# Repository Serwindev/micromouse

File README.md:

# Project Zacch v1

## About the project

Project Zacch is a full-size micromouse whose aim is to solve the maze autonomously.

The name of the mouse actually comes from Bible (Luke 19:1-10). There was a man called Zacchaeus -- who wanted to see Jesus but because he was short, he couldn't able to see Him. So he climbed a tree to see Jesus.

The dimension of Zacch is 90mm x 127mm (3.54 x 5.00 inches). Compared to other mice out there, it isn't that small. But this is my first-ever hardware project and i needed some more space to work properly.

The Project Zacch v1 is a project made for the event ["Fallout"](https://fallout.hackclub.com/) conducted by [HackClub](https://hackclub.com/).

---

## BOM

|sno|product name         |description                                  |Quantity |link                                                                                                                                                                                                                                                                                                                                                                                             |unit price |amount |Running total |   |
|---|---------------------|---------------------------------------------|---------|-------------------------------------------------------------------------------------------------------------------------------------------------------------------------------------------------------------------------------------------------------------------------------------------------------------------------------------------------------------------------------------------------|-----------|-------|--------------|---|
|  1| ESP32               | Brain of the Mouse                          |        1| [link](https://makerbazar.in/products/esp32-wroom-wifi-ble-bluetooth-iot-node-mcu-board?variant=48251049935088)                                                                                                                                                                                                                                                                                         |     445.00| 445.00|        445   |   |
|  2| Motor Driver        | Bridge between Brain and motor              |        1| [link](https://makerbazar.in/products/drv8833-2-channel-1-5a-dc-motor-driver?variant=48341841346800)                                                                                                                                                                                                                                                                                                    |      65.00|  65.00|        510   |   |
|  3| Motors with encoders| Locomotive device to calculate it's position|        2| [link](https://roboticsdna.in/product/n20-6v-500rpm-micro-metal-gear-motor-with-encoder/ )                                                                                                                                                                                                                                                                                                              |     494   | 988   |       1498   |   |
|  4| Infrared Sensors    | Eyes to watch out for obstacles             |        2| [link](https://makerbazar.in/products/ir-receiver-transistor-led?variant=42847315525872)                                                                                                                                                                                                                                                                                                                |      99.00| 198   |       1696   |   |
|  5| Battery             | To power the mouse                          |        1| [link](https://robu.in/product/wly603040-600mah-3-7v-single-cell-rechargeable-lipo-battery/?utm_source=chatgpt.com)                                                                                                                                                                                                                                                                                     |     198   | 198   |       1894   |   |
|  6| MOSFET              | To switch on the IR leds                    |        2| [link](https://www.digikey.in/en/products/detail/alpha-omega-semiconductor-inc/AO3400A/1855772)                                                                                                                                                                                                                                                                                                         |      49.15|  98.30|       1992.3 |   |
|  7| Resistors pack      | TO limit the current                        |        1| [link](https://robu.in/product/30-different-valued-metal-film-resistor-assorted-kit-for-diy-electronic-projects-and-experiments/)                                                                                                                                                                                                                                                                       |     199.00| 199.00|       2191.3 |   |
|  8| Wheels              | Pair of wheels suitable for N20             |        1| [link](https://dyoraarobotics.in/product/2)                                                                                                                                                                                                                                                                                                                                                             |     269   | 269   |       2460.3 |   |
|  9| Caster ball         | Non-driven wheel to support the mouse       |        1| [link](https://makerbazar.in/products/mini-3pi-car-n20-caster-robot-ball-wheel)                                                                                                                                                                                                                                                                                                                         |      39   |  39   |       2499.3 |   |
| 10| Boost converter     | To convert low voltage into 5v              |        1| [link](https://robocraze.com/products/tps61023-3-7a-5v-output-mini-boost-converter-breakout-board-7semi?srsltid=AfmBOorZcjLyfdjhu4-ktQiGOcvzMeDhyjm8kQI_HV5Uemv6zVHmJe5q)                                                                                                                                                                                                                               |      87   |  87   |       2586.3 |   |
| 11| Switch              | To power ON/OFF                             |        1| [link](https://makerbazar.in/products/3-pin-dip-mini-slide-switch-through-hole-pcb-slide-button?variant=46800238575856)                                                                                                                                                                                                                                                                                 |      55   |  55   |       2641.3 |   |
| 12| Screw terminal      | To connect battery                          |        1| [link](https://makerbazar.in/products/wire-to-board-screw-terminal-connectors?srsltid=AfmBOorlYyyEAAogTVcPhF7FhGmk6QyMP0Ij64HXCppaQqRuH7ws5u8H&variant=48816549658864)                                                                                                                                                                                                                                  |      25   |  25   |       2666.3 |   |
| 13| Capacitor 47uF      | Caps to store energy                        |        3| [link](https://www.mouser.in/en/ProductDetail/Panasonic/ECA-1HHG470?qs=sGAEpiMZZMsh%252B1woXyUXj0KTxVgEP8%2FoesVWFq9mWps%3D)                                                                                                                                                                                                                                                                            |      17.89|  53.67|       2719.97|   |
| 14| Capacitor 0.1uF     | Caps                                        |       10| [link](https://robu.in/product/rder71h104k0m1h03a-murata-electronics-%C2%B110-50v-100nf-x7r-pluginp5mm-multilayer-ceramic-capacitors-mlcc-leaded-rohs/?gad_source=1&gad_campaignid=17427802703&gbraid=0AAAAADvLFWefn6i5u6u06P2ikuNaq8nHi&gclid=CjwKCAjwvNfSBhBiEiwAyaGMCc8RoM_25v4rTFsFHUdJuWaXGIPravkARzQQLWtrZbm0opEAT2KkExoCW2IQAvD_BwE)                                                             |      16.00| 160   |       2879.97|   |
| 15| Female headers      | To mount componenets                        |        3| [link](https://makerbazar.in/products/female-berg-strip-2-54mm-header-pin?variant=46822716735728&country=IN&currency=INR&utm_medium=product_sync&utm_source=google&utm_content=sag_organic&utm_campaign=sag_organic&gad_source=1&gad_campaignid=17426677322&gbraid=0AAAAACLxaAblJEnB5dLql7-x3ZBpJzfe3&gclid=CjwKCAjwmdLSBhANEiwAkREMN3OXcRsLFpE1FGKxTkcoRNSS2PXJgUW0fRO1fCnhbYDCYuGI9XgbIRoCBOQQAvD_BwE)|       8.5 |  25.50|       2905.47|   |
| 16| Male headers        | To mount components                         |        2| [link](https://makerbazar.in/products/berg-strip-40-pins?variant=49811925532912&country=IN&currency=INR&utm_medium=product_sync&utm_source=google&utm_content=sag_organic&utm_campaign=sag_organic&gad_source=1&gad_campaignid=17426677322&gbraid=0AAAAACLxaAblJEnB5dLql7-x3ZBpJzfe3&gclid=CjwKCAjwmdLSBhANEiwAkREMNz77SH8W3c11Vlf4g-hZFOluHlT7KyqQvG2HieT2qgm2LeFkTQocnRoCc5MQAvD_BwE)                 |      25   |  50   |       2955.47|   |
| 17| Tactile switch      | To actually make mouse move                 |        1| [link](https://makerbazar.in/products/small-push-button-switch?srsltid=AfmBOoqmTbENfx2a-pJnI3aoowbEo9liCWUeOjVfWND0_L68pnGFyOcG)                                                                                                                                                                                                                                                                        |      20   |  20   |       2975.47|   |
| 18  | PCB                  | Acts as a chassis as well as electrical circuit | 1        | wherever you prefer                                                                                                                                                                                                                                                                                                                                                                              | 3500       | 3500   | 6475.47       |   |
| 19  | 3d print             | Mounts for motors                               | 2        | wherever you prefer (use assets/CAD_design/Motot_mount.stp)                                                                                                                                                                                                                                                                                                                                      | 500        | 1000   | 7475.47       |   |

---

## Project Workflow

I have actually journalled everything from Day 1 till the end -- you can find them in the **Devlogs folder**.

#### Research and Development

- On the Day 1, i worked on researching the requirments for the project.
- On further days, i sourced online to find the suitable products and built the BOM (Bill of materials) -- which you can find [here](components/BOM.csv) and also sketched a very rough diagram about the wiring.

---

#### Schematic 

- From day 4, i worked on the Schematic design in Kicad. It's my very first time and i found it kinda hard at first.
- After some several iterations and struggles, with the help of chatGPT, i finished the 1st version of schematic on day 7

---

#### CAD design

- From Day 8, i worked on the CAD design of this project in Tinkercad
- After two days of CAD'ing, i somehow managed to capture the vision in my mind into the Screen. (Spoiler alert: Final result isn't the same as here)

---

#### PCB design

- After the completion of CAD design, i started to add footprints for all the componenets in kicad.
- I found it hard to understand the way footprint works in the consecutive days.
- During these days, i changed the IR sensors - from modules to separate transmiter. (Reason: Because the module provides only True or False output based on whether the obstacle is near or not)
- I completed the whole routing of PCB by the day 20, but then i found that esp32 has been misaligned and needs to be re-aligned.
- After two days of debugging, i completed the PCB (But still, I thought of adding some LED's into the PCB and mounting Pads for caster ball)

##### Front copper

##### Back copper

##### Final routing 

PS: There's an easter egg in the PCB -- if you can find it out and DM me for prizes!! 
Instagram: [@serwin.dev](https://www.instagram.com/serwin.dev)

---

### Features

- Project Zacch uses two driven wheels and a non-driven caster ball for locomotion.
- It uses IR sensors and transmitter to wall sensing mechanism.

---

## How to build?!

- Step 1: Check whether you have all the components
- Step 2: Order PCB and wait -- take some rest
- Step 3: Quickly assemble all the parts
- Step 4: Run firmware and GOOO!!!!

---

### Future works

- Once the build is successful, the firmware of the project will commence.
- Using PID for staying in the center of the line.

---

### Contributors

- [@Serwindev](https://github.com/Serwindev)

---

### Resources

- [Ojasp21/micromouse](https://github.com/Ojasp21/Micromouse/tree/main)
- [Mushak/micromouse](https://github.com/gautam-dev-maker/mushak/tree/main)

---

### Special Credits

- All thanks to HackClub for making this project came into life through [Fallout](https://fallout.hackclub.com/)

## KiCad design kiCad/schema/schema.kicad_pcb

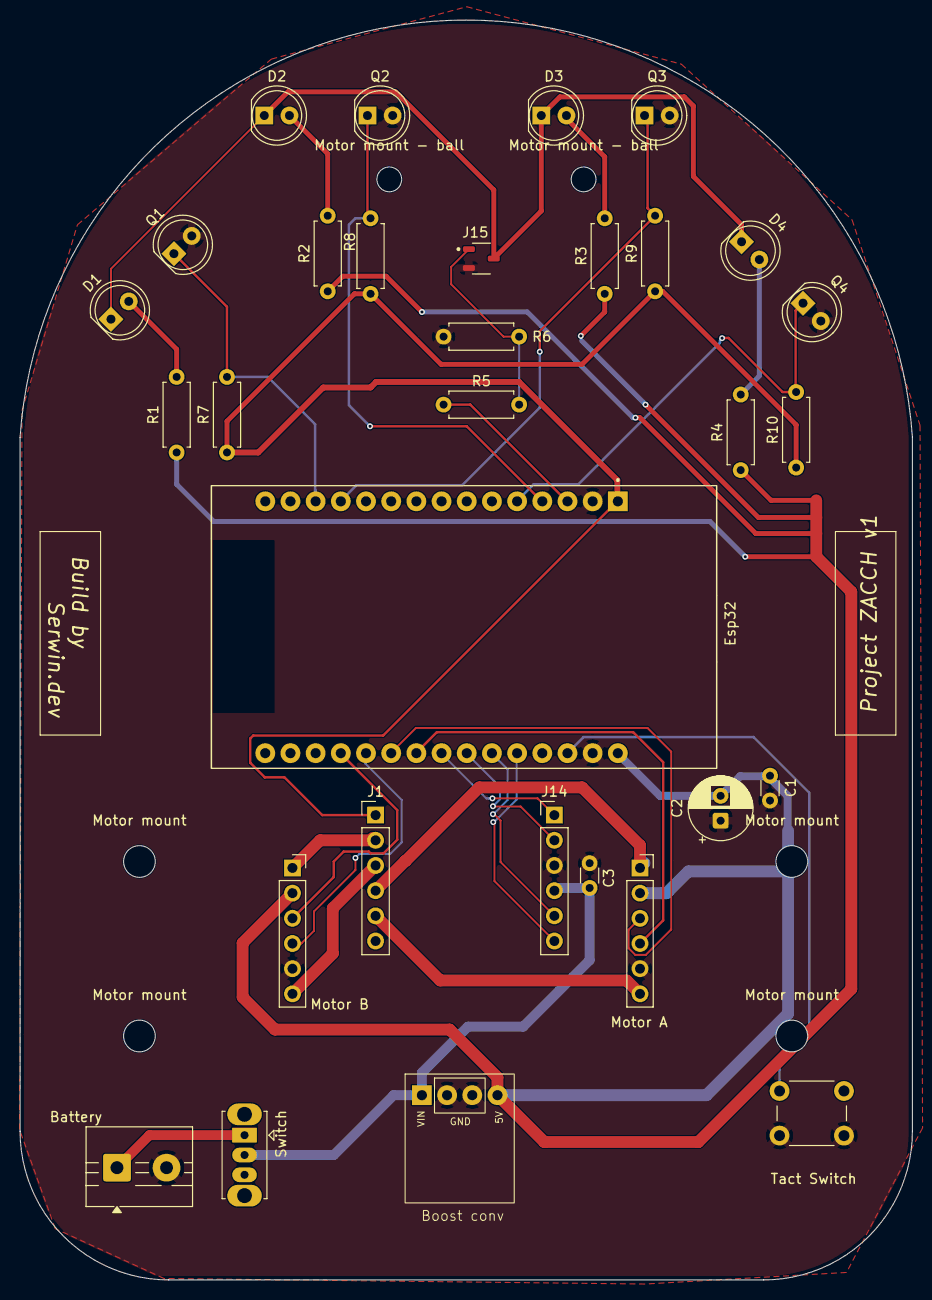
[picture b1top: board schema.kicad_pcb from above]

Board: 2 copper layers, 90.0 x 127.1 mm, 37 parts (0 on the bottom side), 29 nets.

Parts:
Battery: Bat; TerminalBlock_MaiXu_MX126-5.0-02P_1x02_P5.00mm
Boost conv: BOOST; TPS61023
C1, C3: C 0.1; C_Disc_D3.0mm_W1.6mm_P2.50mm
C2: C_Polarized 47; CP_Radial_D6.3mm_P2.50mm
D1, D2, D3, D4: LED; LED_D5.0mm_Clear
Esp32: Esp32; MODULE_ESP32_DEVKIT_V1
J1: DRV8833; PinHeader_1x06_P2.54mm_Vertical
J14: GND; PinHeader_1x06_P2.54mm_Vertical
J15: MOSFET; SOT95P280X125-3N
Motor A: M2 Left; PinSocket_1x06_P2.54mm_Vertical
Motor B: M1 Right; PinSocket_1x06_P2.54mm_Vertical
Motor mount: MountingHole_3.2mm_M3
Motor mount - ball: MountingHole_2.5mm
Motor mount - ball#2: MountingHole_2.5mm
Motor mount#2, Motor mount#3, Motor mount#4: MountingHole_3.2mm_M3
Q1, Q2, Q3, Q4: Q_Photo_NPN; LED_D5.0mm_Clear
R1, R2, R3, R4: 120 ohm; R_Axial_DIN0207_L6.3mm_D2.5mm_P7.62mm_Horizontal
R5: 100 ohm; R_Axial_DIN0207_L6.3mm_D2.5mm_P7.62mm_Horizontal
R6: 100k ohm; R_Axial_DIN0207_L6.3mm_D2.5mm_P7.62mm_Horizontal
R7, R8, R9, R10: 10k ohm; R_Axial_DIN0207_L6.3mm_D2.5mm_P7.62mm_Horizontal
Switch: Switch; SW_Slide_SPDT_Straight_CK_OS102011MS2Q
Tact Switch: Tact Switch; SW_PUSH_6mm_H5mm

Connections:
/3V3: Esp32.1, J1.1, R7.1, R8.1, R9.1, R10.1
/AIN 1: Esp32.23, J14.1
/AIN 2: Esp32.24, J14.2
/AOUT 1: J1.2, Motor B.1
/AOUT 2: J1.3, Motor B.6
/BAT +: Boost conv.1, C3.1, J14.4, Switch.2
/BAT R+: Battery.1, Switch.1
/BIN 1: Esp32.25, J14.5
/BIN 2: Esp32.26, J14.6
/BOOST +: Boost conv.4, C1.1, C2.2, Esp32.30, Motor A.2, Motor B.2, R1.1, R2.1, R3.1, R4.1
/BOUT 1: J1.4, Motor A.1
/BOUT 2: J1.5, Motor A.6
/ENC A1: Esp32.19, Motor B.3
/ENC A2: Esp32.20, Motor B.4
/ENC B1: Esp32.21, Motor A.3
/ENC B2: Esp32.22, Motor A.4
/GND: Battery.2, Boost conv.2, Boost conv.3, C1.2, C2.1, C3.2, Esp32.2, Esp32.29, J14.3, J15.2, Motor A.5, Motor B.5, Q1.2 (E), Q2.2 (E), Q3.2 (E), Q4.2 (E), R6.1, Tact Switch.2
/IR 1: Esp32.13, Q1.1 (C), R7.2
/IR 2: Esp32.4, Q2.1 (C), R8.2
/IR 3: Esp32.12, Q3.1 (C), R9.2
/IR 4: Esp32.5, Q4.1 (C), R10.2
/IR EM: Esp32.3, R5.1
/SW PIN: Esp32.28, Tact Switch.1
unnamed: D1.2 (A), R1.2
unnamed: D1.1 (K), D2.1 (K), D3.1 (K), D4.1 (K), J15.3
unnamed: D2.2 (A), R2.2
unnamed: D3.2 (A), R3.2
unnamed: D4.2 (A), R4.2
unnamed: J15.1, R5.2, R6.2

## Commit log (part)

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2026-05-20 Day one
2026-05-20 BOM added
2026-05-22 Day-2 completed
2026-05-24 Day 3
2026-05-24 Day 4 -- Schematic design
2026-05-27 Day 4
2026-05-27 Day 5
2026-05-27 Day 6
2026-05-27 Day 6 - Schematics
2026-05-28 Day 7 - Schematics finished
2026-05-29 Day 8 - Research, CAD design
2026-06-01 Day 9 - CAD design
2026-06-02 Day 10 - CAD design, PCB design started
2026-06-06 Day 11 -- PCB, footprints, headache
2026-06-27 Day 12 -- Resuming the project
2026-06-28 Day 13 -- IR leds, footprints
2026-06-29 Day 14 -- whole schematics done with footprints
2026-06-30 Day 14 -- PCB layout
